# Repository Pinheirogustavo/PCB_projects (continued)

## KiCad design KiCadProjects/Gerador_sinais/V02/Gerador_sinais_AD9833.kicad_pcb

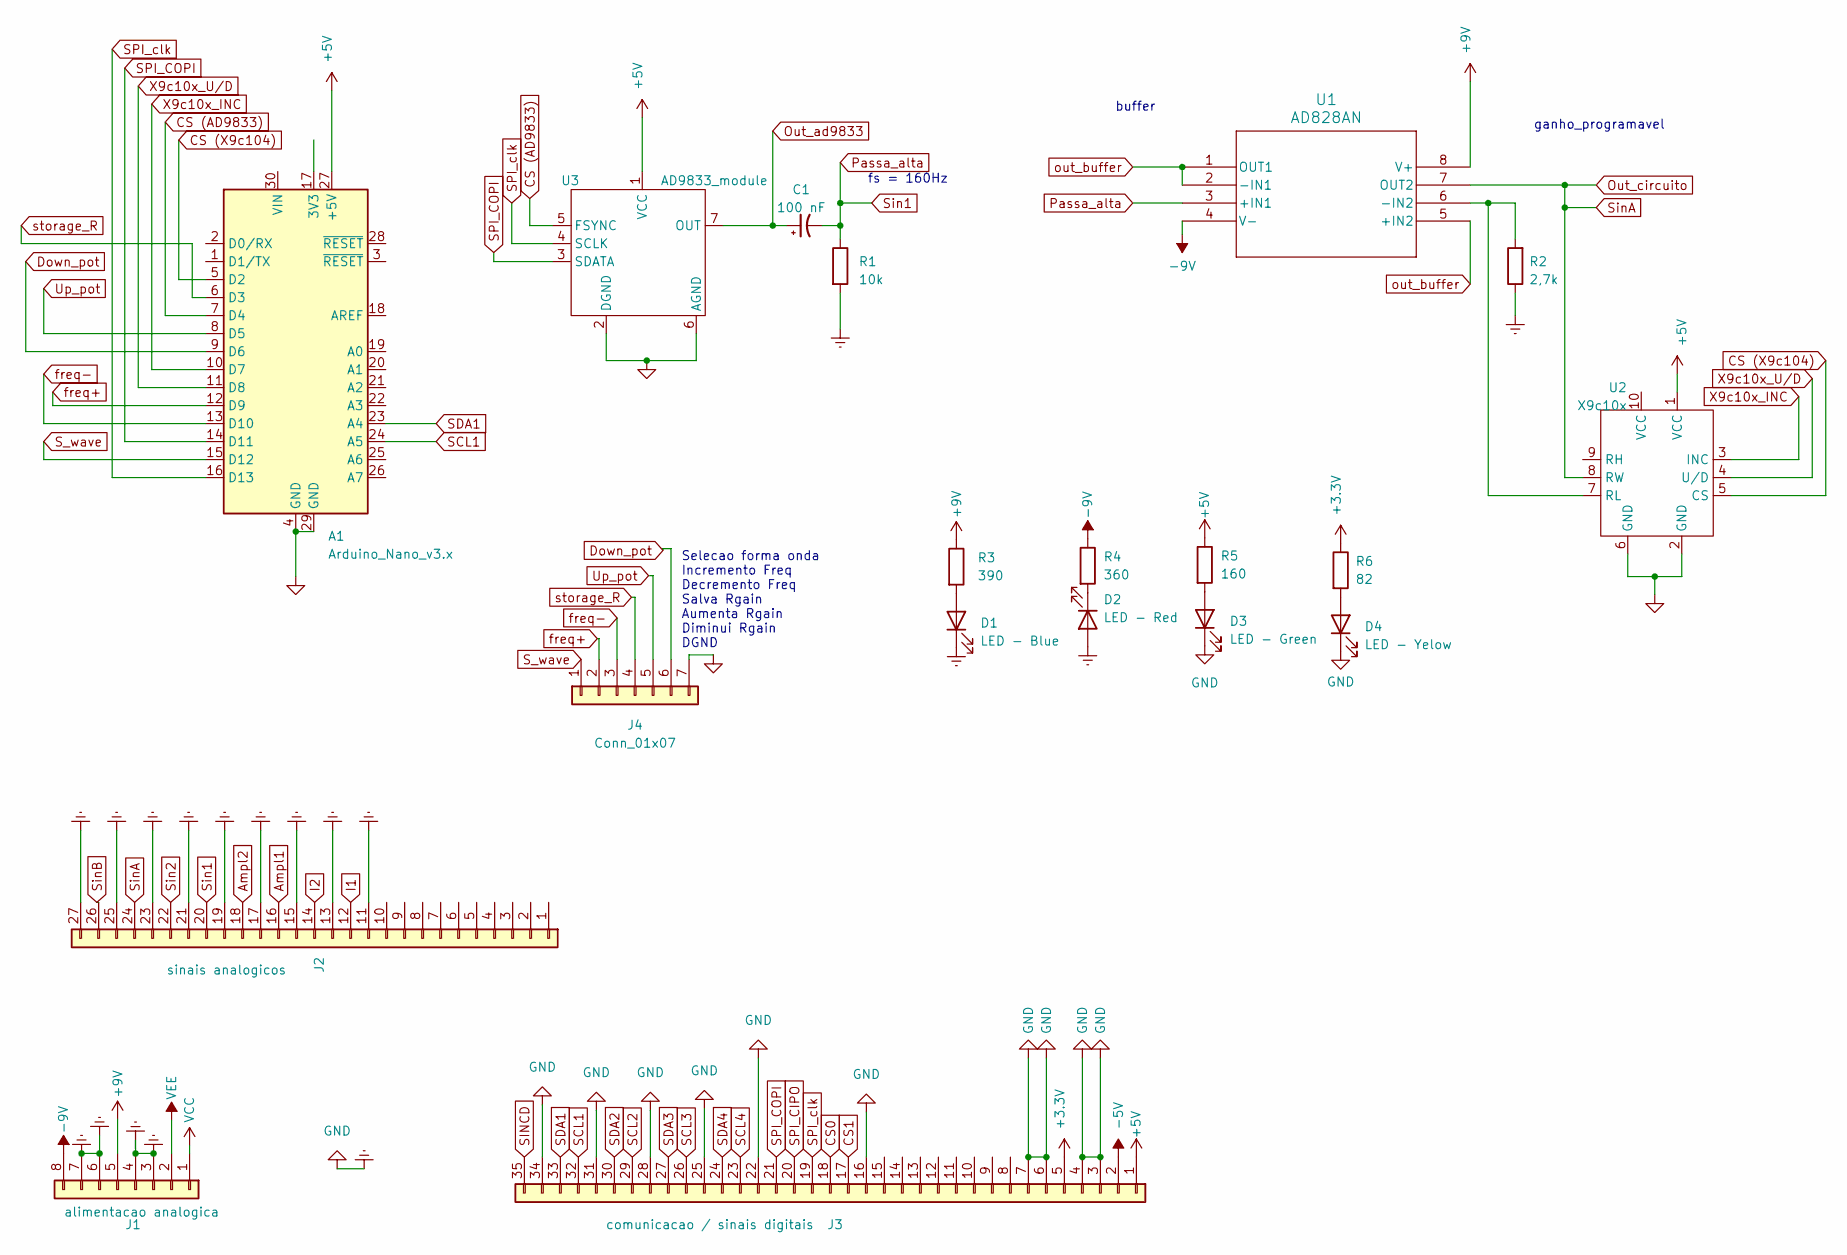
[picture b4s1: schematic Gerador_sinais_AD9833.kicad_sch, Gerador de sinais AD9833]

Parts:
A1: Arduino_Nano_v3.x; Arduino_Nano
C1: 100 nF; CP_Radial_D5.0mm_P2.50mm
D1: LED - Blue; LED_D5.0mm
D2: LED - Red; LED_D5.0mm
D3: LED - Green; LED_D5.0mm
D4: LED - Yelow; LED_D5.0mm
J1: alimentacao analogica; PinHeader_1x08_P2.54mm_Vertical
J2: sinais analogicos; PinHeader_1x27_P2.54mm_Vertical
J3: comunicacao / sinais digitais; PinHeader_1x35_P2.54mm_Vertical
J4: Conn_01x07; PinHeader_1x07_P2.54mm_Horizontal
R1: 10k; R_Axial_DIN0204_L3.6mm_D1.6mm_P5.08mm_Horizontal
R2: 2,7k; R_Axial_DIN0204_L3.6mm_D1.6mm_P5.08mm_Horizontal
R3: 390; R_Axial_DIN0207_L6.3mm_D2.5mm_P7.62mm_Horizontal
R4: 360; R_Axial_DIN0207_L6.3mm_D2.5mm_P7.62mm_Horizontal
R5: 160; R_Axial_DIN0207_L6.3mm_D2.5mm_P7.62mm_Horizontal
R6: 82; R_Axial_DIN0207_L6.3mm_D2.5mm_P7.62mm_Horizontal
U1: AD828AN; AD828
U2: X9c10x; X9c10X_module
U3: AD9833_module

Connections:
+3.3V: J3.5, R6.1
+5V: A1.27 (+5V), J3.1, R5.1, U2.1 (VCC), U3.1 (VCC)
+9V: J1.5, R3.1, U1.8 (V+)
-5V: J3.2
-9V: J1.8, R4.1, U1.4 (V-)
Ampl1: J2.16
Ampl2: J2.18
CS0: J3.18
CS1: J3.17
CS (AD9833): A1.7 (D4), U3.5 (FSYNC)
CS (X9c104): A1.5 (D2), U2.5 (CS)
Down_pot: A1.9 (D6), J4.6
Earth: A1.4 (GND), A1.29 (GND), D1.1 (K), D2.2 (A), D3.1 (K), D4.1 (K), J1.3, J1.4, J1.6, J1.7, J2.11, J2.13, J2.15, J2.17, J2.19, J2.21, J2.23, J2.25, J2.27, J3.3, J3.4, J3.6, J3.7, J3.16, J3.22, J3.25, J3.28, J3.31, J3.34, J4.7, R1.2, R2.1, U2.2 (GND), U2.6 (GND), U3.2 (DGND), U3.6 (AGND)
I1: J2.12
I2: J2.14
unnamed: D1.2 (A), R3.2
unnamed: D2.1 (K), R4.2
unnamed: D3.2 (A), R5.2
unnamed: D4.2 (A), R6.2
unnamed: R2.2, U1.6 (-IN2), U2.7 (RL)
Out_ad9833: C1.1, U3.7 (OUT)
Out_circuito: J2.24, U1.7 (OUT2), U2.8 (RW)
Passa_alta: C1.2, J2.20, R1.1, U1.3 (+IN1)
SCL1: A1.24 (A5), J3.32
SCL2: J3.29
SCL3: J3.26
SCL4: J3.23
SDA1: A1.23 (A4), J3.33
SDA2: J3.30
SDA3: J3.27
SDA4: J3.24
SINCD: J3.35
SPI_CIPO: J3.20
SPI_COPI: A1.14 (D11), J3.21, U3.3 (SDATA)
SPI_clk: A1.16 (D13), J3.19, U3.4 (SCLK)
S_wave: A1.15 (D12), J4.1
Sin2: J2.22
SinB: J2.26
Up_pot: A1.8 (D5), J4.5
VCC: J1.1
VEE: J1.2
X9c10x_INC: A1.10 (D7), U2.3 (INC)
X9c10x_U/D: A1.11 (D8), U2.4 (U/D)
freq+: A1.12 (D9), J4.2
freq-: A1.13 (D10), J4.3
out_buffer: U1.1 (OUT1), U1.2 (-IN1), U1.5 (+IN2)
storage_R: A1.6 (D3), J4.4

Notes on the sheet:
ganho_programavel
fs = 160Hz
buffer
Selecao forma onda Incremento Freq Decremento Freq Salva Rgain Aumenta Rgain Diminui Rgain DGND

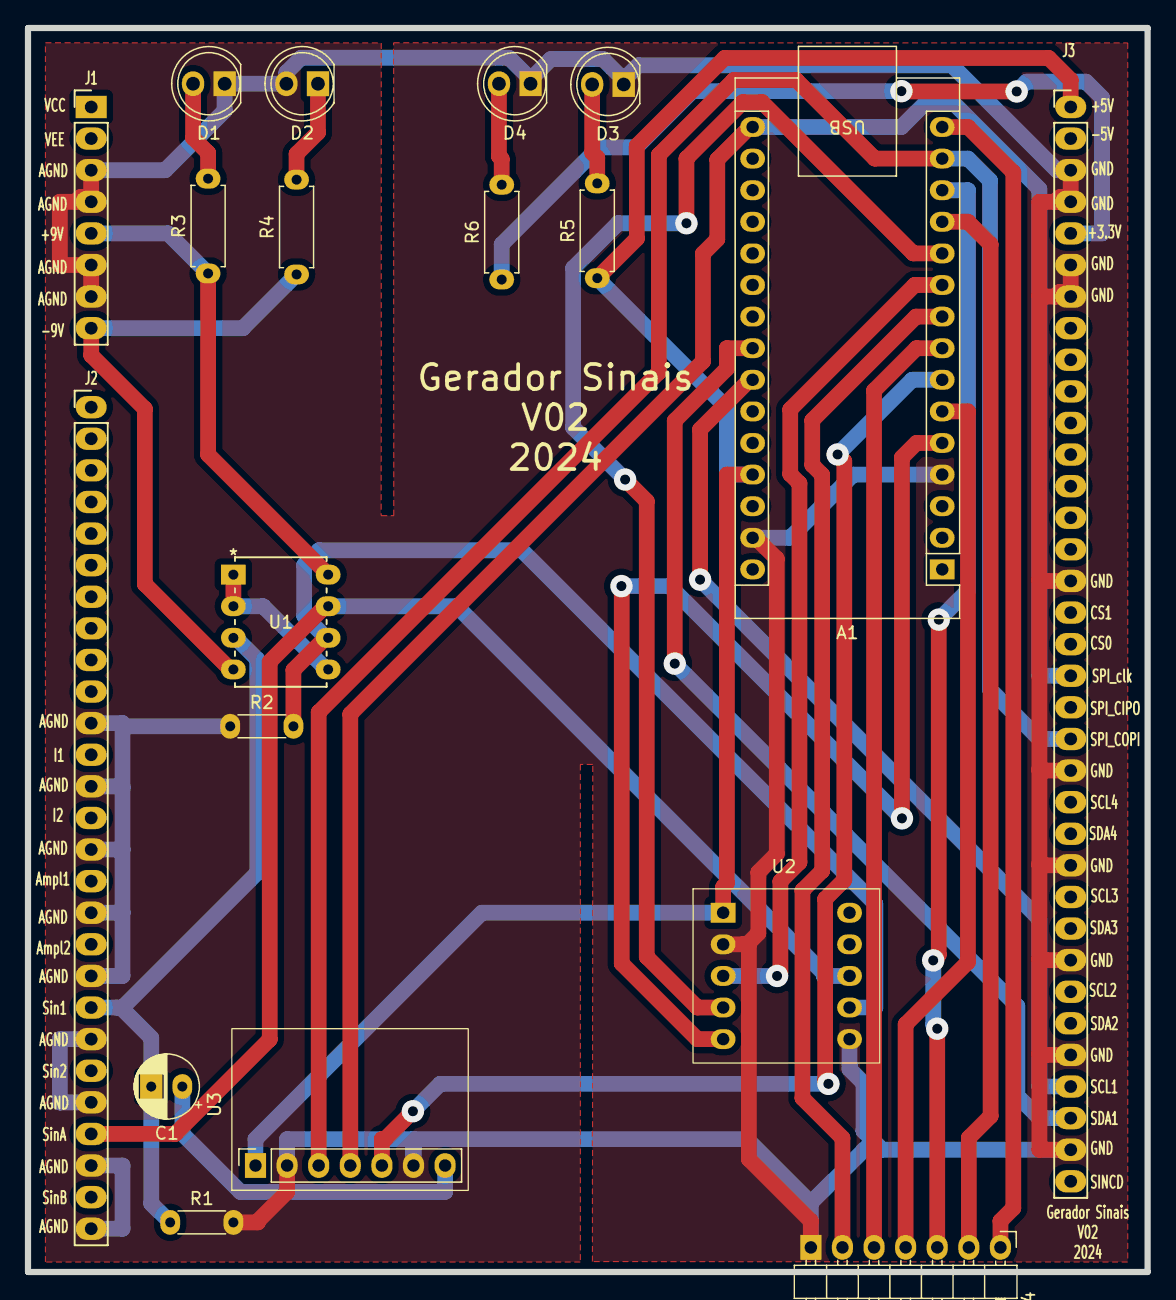
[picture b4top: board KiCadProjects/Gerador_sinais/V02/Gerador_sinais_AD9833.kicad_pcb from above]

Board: 2 copper layers, 90.0 x 100.0 mm, 19 parts (0 on the bottom side), 28 nets.

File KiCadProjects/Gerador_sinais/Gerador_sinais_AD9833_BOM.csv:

"Id";"Designador";"Footprint";"Quantidade";"Designação";"Fornecedor e referência";
1;"U2";"X9c10X_module";1;"X9c10x";;;
2;"SW3";"SW_BUTT-2";1;"botao_decremento_freq";;;
3;"C1";"CP_Radial_D5.0mm_P2.50mm";1;"100 nF";;;
4;"A1";"Arduino_Nano";1;"Arduino_Nano_v3.x";;;
5;"U1";"N_8_ADI";1;"AD828AN";;;
6;"SW4";"SW_BUTT-2";1;"botao_save_Rgain";;;
7;"J4";"PinHeader_1x35_P2.54mm_Vertical";1;"comunicacao / sinais digitais";;;
8;"SW6";"SW_BUTT-2";1;"botao_diminui_Rgain";;;
9;"R2";"R_Axial_DIN0204_L3.6mm_D1.6mm_P5.08mm_Horizontal";1;"2,7k";;;
10;"J1";"PinHeader_1x08_P2.54mm_Vertical";1;"tensoes";;;
11;"J3";"PinHeader_1x27_P2.54mm_Vertical";1;"sinais analogicos";;;
12;"U3";"AD9833_module";1;"AD9833_module";;;
13;"SW2";"SW_BUTT-2";1;"botao_incremento_freq";;;
14;"SW1";"SW_BUTT-2";1;"botao_forma_onda";;;
15;"R1";"R_Axial_DIN0204_L3.6mm_D1.6mm_P5.08mm_Horizontal";1;"10k";;;
16;"SW5";"SW_BUTT-2";1;"botao_aumenta_Rgain";;;

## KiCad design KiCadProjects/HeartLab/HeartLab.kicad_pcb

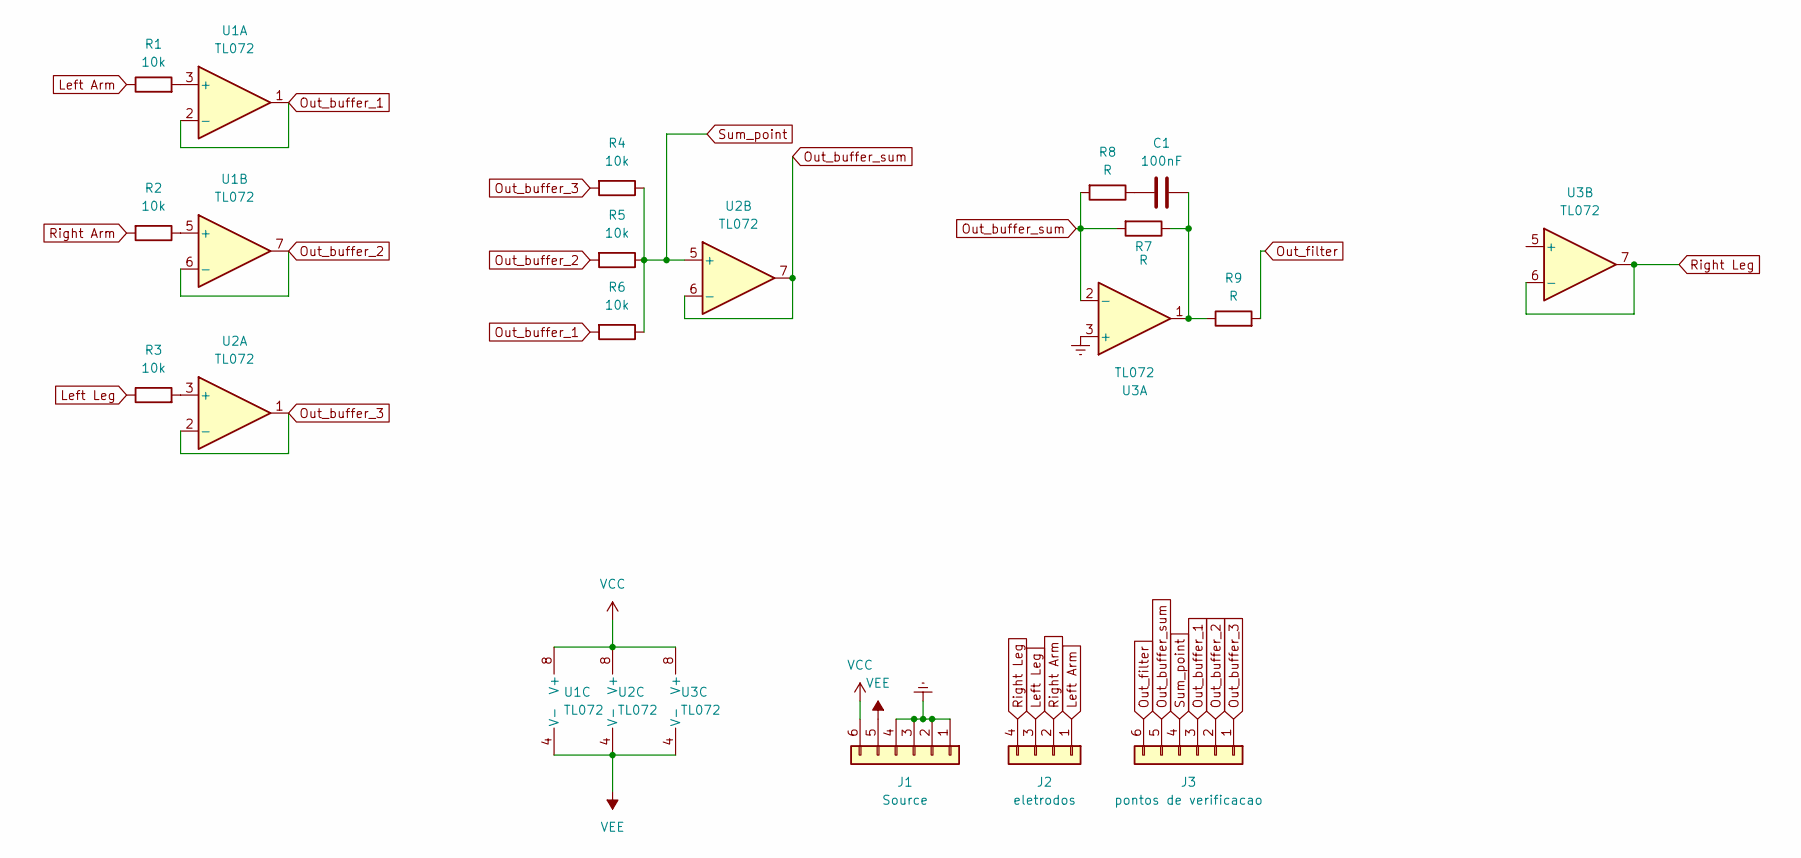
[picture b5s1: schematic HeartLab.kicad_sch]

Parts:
C1: 100nF; C_Disc_D3.0mm_W1.6mm_P2.50mm
J1: Source; PinHeader_1x06_P2.54mm_Vertical
J2: eletrodos; PinHeader_1x04_P2.54mm_Vertical
J3: pontos de verificacao; PinHeader_1x06_P2.54mm_Vertical
R1, R2, R3, R4, R5, R6: 10k; R_Axial_DIN0207_L6.3mm_D2.5mm_P7.62mm_Horizontal
R7, R8, R9: R; R_Axial_DIN0207_L6.3mm_D2.5mm_P7.62mm_Horizontal
U1, U2, U3: TL072; P8

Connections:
Earth: J1.1, J1.2, J1.3, J1.4, U3.3 (+)
Left Arm: J2.1, R1.1
Left Leg: J2.3, R3.1
unnamed: C1.1, R7.1, R9.1, U3.1
unnamed: C1.2, R8.1
unnamed: R1.2, U1.3 (+)
unnamed: R2.1, U1.5 (+)
unnamed: R3.2, U2.3 (+)
Out_buffer_1: J3.3, R6.2, U1.1, U1.2 (-)
Out_buffer_2: J3.2, R5.2, U1.6 (-), U1.7
Out_buffer_3: J3.1, R4.2, U2.1, U2.2 (-)
Out_buffer_sum: J3.5, R7.2, R8.2, U2.6 (-), U2.7, U3.2 (-)
Out_filter: J3.6, R9.2
Right Arm: J2.2, R2.2
Right Leg: J2.4, U3.6 (-), U3.7
Sum_point: J3.4, R4.1, R5.1, R6.1, U2.5 (+)
VCC: J1.6, U1.8 (V+), U2.8 (V+), U3.8 (V+)
VEE: J1.5, U1.4 (V-), U2.4 (V-), U3.4 (V-)

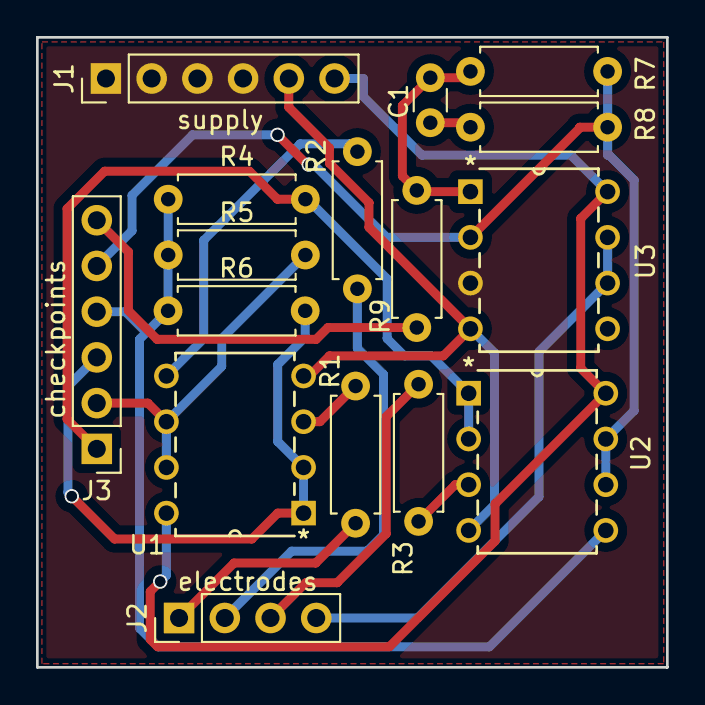
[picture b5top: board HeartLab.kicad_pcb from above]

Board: 2 copper layers, 35.0 x 35.0 mm, 16 parts (0 on the bottom side), 18 nets.

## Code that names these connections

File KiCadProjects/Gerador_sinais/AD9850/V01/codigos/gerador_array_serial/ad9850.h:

/*
 * Funções para uso do gerador de onda senoidal (DDS) AD9850.
 * Baseado em https://www.electrodragon.com/w/AD9850_Module_DDS_Signal_Generator_V2
 * 
 * Autor: Erick León
 * 

#define W_CLK PA5   //  - connect to AD9850 module word load clock pin (CLK)
#define FQ_UD PA4   //  - connect to freq update pin (FQ)
#define DATA  PA3   //  - connect to serial data load pin (DATA)
#define RESET PA2   //  - connect to reset pin (RST)

*/

#define W_CLK PC14   //  - connect to AD9850 module word load clock pin (CLK)
#define FQ_UD PC15   //  - connect to freq update pin (FQ)
#define DATA  PA0   //  - connect to serial data load pin (DATA)
#define RESET PA1   //  - connect to reset pin (RST)

#define _pulseHigh(pin) {digitalWrite(pin, HIGH); digitalWrite(pin, LOW); }

// transfers a byte, a bit at a time, LSB first to the 9850 via serial DATA line
void _tfr_byte(byte data){
    for (int i=0; i<8; i++, data>>=1) {
        digitalWrite(DATA, data & 0x01);
        _pulseHigh(W_CLK); //after each bit sent, CLK is pulsed high
    }
}



// frequency calc from datasheet page 8 = <sys clock> * <frequency tuning word>/2^32
void ad9850_sendFrequency(double frequency) {
    int32_t freq = frequency * 4294967295/125000000; // note 125 MHz clock on 9850
    for (int b=0; b<4; b++, freq>>=8) {
        _tfr_byte(freq & 0xFF);
    }
    _tfr_byte(0x000);  // Final control byte, all 0 for 9850 chip
    _pulseHigh(FQ_UD); // Done! Should see output
}

void ad9850_setup() {
    pinMode(FQ_UD, OUTPUT);
    pinMode(W_CLK, OUTPUT);
    pinMode(DATA, OUTPUT);
    pinMode(RESET, OUTPUT);
    _pulseHigh(RESET);
    _pulseHigh(W_CLK);
    _pulseHigh(FQ_UD); // this pulse enables serial mode - Datasheet page 12 figure 10
}
